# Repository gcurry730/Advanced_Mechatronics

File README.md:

# ME 433: Advanced Mechatronics

Gale Curry

3/31/16

This repository contains my code written for the course [ME 433](http://www.mccormick.northwestern.edu/mechanical/courses/descriptions/433-advanced-mechatronics.html) at Northwestern University. 
Most projects use the [PIC32MX250F128B](http://ww1.microchip.com/downloads/en/DeviceDoc/60001168H.pdf) microcontroller. 

### *HW 1*: **Breadboard Circuitry**
* Building a PIC32 circuit with voltage regulator + Hello World. 

### *HW 2 & 3*: **PCB Design**
* Design a PCB of the PIC32 circuit in EAGLE. 

### *HW 4*: **SPI & I2C Communication**
* Using SPI to communicate with a [MCP4902 DAC](http://www.microchip.com/wwwproducts/en/MCP4902). 
 
* Using I2C to communicate with a [MCP23008](http://www.microchip.com/wwwproducts/en/MCP23008) I/O pin expander.

### *HW 5*: **LCD**
* Writing Hello World to LCD. [128 x 128 pixel TFT LCD](http://www.gearbest.com/lcd-led-display-module/pp_219125.html)

### *HW 6*: **IMU**
* Read the [LSM6DS33](https://www.pololu.com/product/2736) IMU and write values to LCD. 

### *HW 7*: **USB**
* [MPLAB Harmony](http://www.microchip.com/mplab/mplab-harmony) project with USB; make the PIC32 enumerate as a mouse

### *HW 8*: **CDC**
* [MPLAB Harmony](http://www.microchip.com/mplab/mplab-harmony) CDC project; use PUTTY to send an int to the PIC32, and have it return the int

### *HW 9*: **Android Development**
* Write an Anrdoid App (Hello World). 

### *HW 10*: **3D Printing**
* Use CAD to make a wheel hub for your motor and o-ring. 3D print it.

### HW 11: **Laser Cutting**
* CAD a 3-sided box and laser cut it.

### *HW 12*: **Camera App**
* Write an Android app that uses the camera to identify the center of a brown line drawn on a green background.

### *HW 13*: **Android - CDC Communication**
* Write an Android app that communicates with a PIC32 CDC device.  

### *HW 14*: **Android - CDC Communication**  
* Write an Android app that mixes the camera and CDC apps together. 

### *HW 15*: **Motor Control** 
* Final line-following robot code. Final robot design.

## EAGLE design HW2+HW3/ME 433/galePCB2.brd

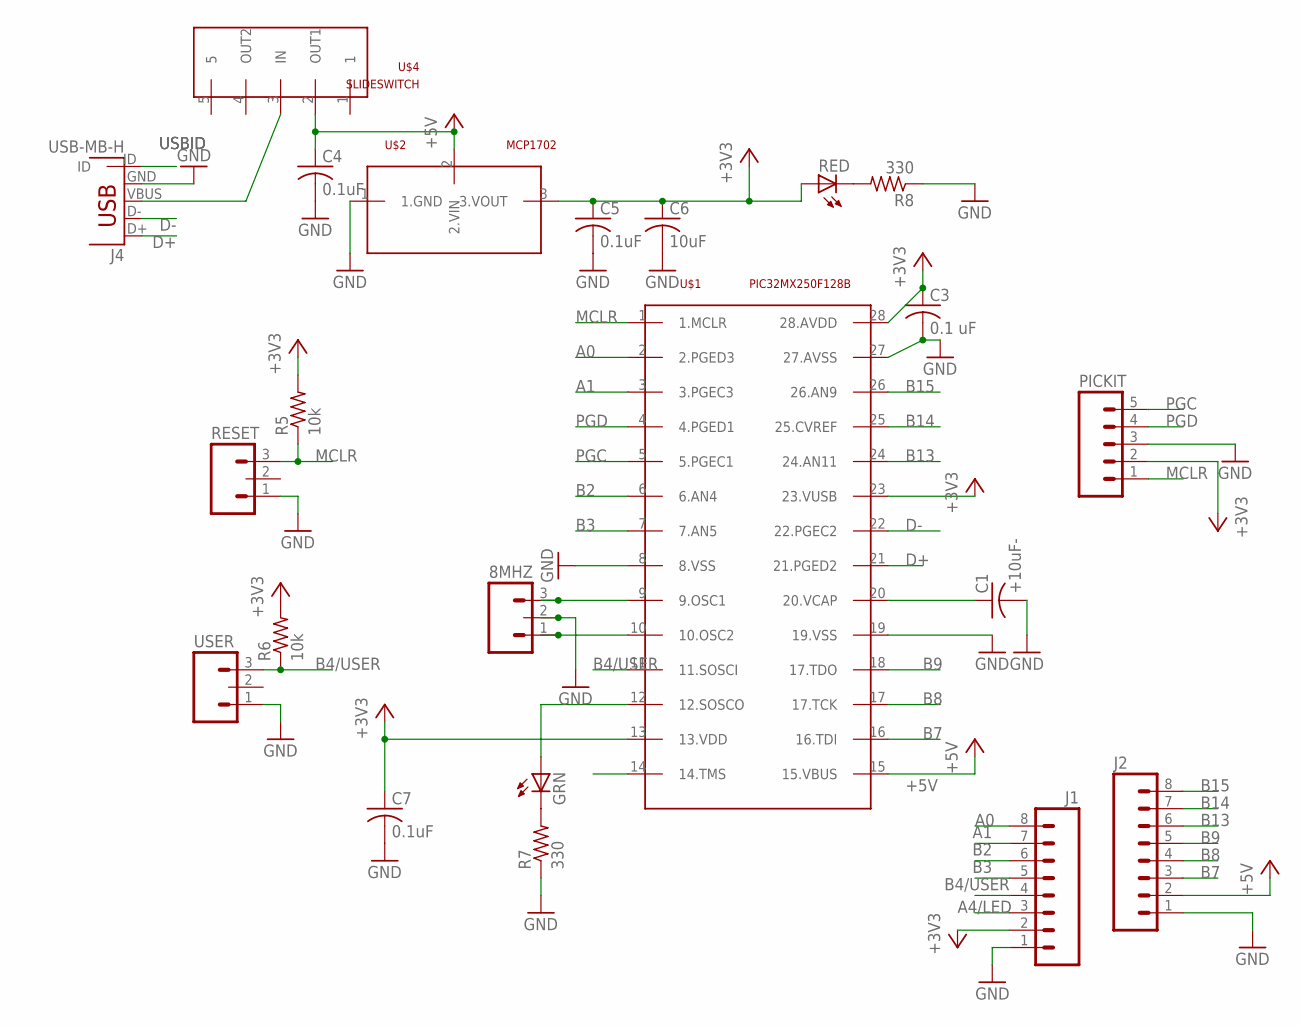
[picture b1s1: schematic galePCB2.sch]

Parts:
8MHZ: M03PTH; 1X03
C1: +10uF-; C025-024X044
C3: 0.1 uF; C025-024X044
C4, C5, C7: 0.1uF; C025-024X044
C6: 10uF; C025-024X044
GRN: LED3MM
J1, J2: M08; 1X08_ROUND
J4: USB-MB-H
PICKIT: M05PTH; 1X05
R5, R6: 10k; 0207/10
R7, R8: 330; 0207/10
RED: LED3MM
RESET: M03LOCK; 1X03_LOCK
U$1: PIC32MX250F128B; DIL28-3
U$2: MCP1702; TO92
U$4: SLIDESWITCH
USER: M03LOCK; 1X03_LOCK

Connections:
+3V3: C3.1, C5.1, C6.1, C7.1, J1.2, PICKIT.2, R5.2, R6.2, RED.A, U$1.13 (13.VDD), U$1.23 (23.VUSB), U$1.28 (28.AVDD), U$2.3 (3.VOUT)
+5V: C4.1, J2.2, U$1.15 (15.VBUS), U$2.2 (2.VIN), U$4.2 (OUT1)
A0: J1.8, U$1.2 (2.PGED3)
A1: J1.7, U$1.3 (3.PGEC3)
A4/LED: GRN.A, J1.3, U$1.12 (12.SOSCO)
B2: J1.6, U$1.6 (6.AN4)
B3: J1.5, U$1.7 (7.AN5)
B4/USER: J1.4, R6.1, U$1.11 (11.SOSCI), USER.3
B7: J2.3, U$1.16 (16.TDI)
B8: J2.4, U$1.17 (17.TCK)
B9: J2.5, U$1.18 (17.TDO)
B13: J2.6, U$1.24 (24.AN11)
B14: J2.7, U$1.25 (25.CVREF)
B15: J2.8, U$1.26 (26.AN9)
D+: J4.D+, U$1.21 (21.PGED2)
D-: J4.D-, U$1.22 (22.PGEC2)
GND: 8MHZ.2, C1.2, C3.2, C4.2, C5.2, C6.2, C7.2, J1.1, J2.1, J4.GND, PICKIT.3, R7.1, R8.1, RESET.1, U$1.8 (8.VSS), U$1.19 (19.VSS), U$1.27 (27.AVSS), U$2.1 (1.GND), USER.1
MCLR: PICKIT.1, R5.1, RESET.3, U$1.1 (1.MCLR)
unnamed: C1.1, U$1.20 (20.VCAP)
unnamed: 8MHZ.3, U$1.9 (9.OSC1)
unnamed: 8MHZ.1, U$1.10 (10.OSC2)
unnamed: R8.2, RED.K (C)
unnamed: GRN.K (C), R7.2
PGC: PICKIT.5, U$1.5 (5.PGEC1)
PGD: PICKIT.4, U$1.4 (4.PGED1)
USBID: J4.ID, U$1.14 (14.TMS)
VBUS: J4.VBUS, U$4.3 (IN)

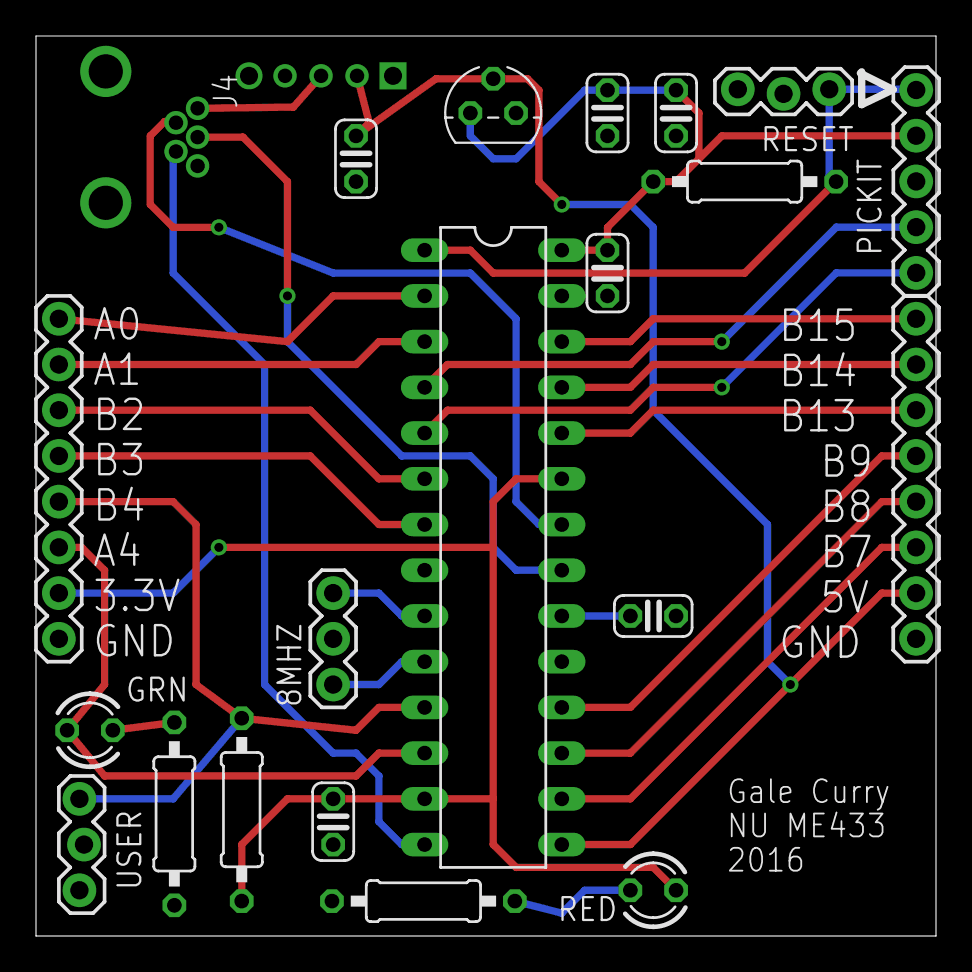
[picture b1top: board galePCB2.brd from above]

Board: 2 copper layers, 50.0 x 50.0 mm, 22 parts (1 on the bottom side), 27 nets.

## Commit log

2016-03-31 :circus_tent: Added .gitattributes & .gitignore files
2016-03-31 My first commit!
2016-03-31 Tester commit to see changes
2016-04-01 added scope pic for part 2
2016-04-01 Added scope photos as I added capacitors
    The first two each smoothed the oscillations more as I added them, the
    last one I added didn't make a noticeable difference
2016-04-04 Added picture of actual PIC32 circuit on breadboard
2016-04-04 Created a blank file for HW1 code
2016-04-04 added header files
2016-04-04 added values to #pragma values
2016-04-04 Made project file through MPLAB IDE
    Created a project in the IDE called HW1, made a main.c file and copied
    over my code that I was writing in the notepad
2016-04-05 complied code, first try
2016-04-05 Added circuit diagram
2016-04-06 added schematic in HW2 folder and updated HW1 code
2016-04-08 updated code
2016-04-08 Moved project into file, added completed library
2016-04-08 Added complete schematic
2016-04-14 Updated schematic % started making board layout
2016-04-14 Continued editing of board
    changed crystal oscillator to a M03, made all resistors smaller
2016-04-14 Finished Board positioning
    Flipped one of the M08 header pins around to align with given
    measurements, changed PICkit to a 5 pin header
2016-04-14 Board Fully connected
    May need to rotate switch, and need to write pin names on back of board
2016-04-14 making gerber files
2016-04-14 Ready to be checked before order
2016-04-18 Began HW4
    created I2C file with given code, started SPI file with functions that
    will be needed
2016-04-19 Moved files into MPLAB IDE and compiled
    finished functions for SPI communication
2016-04-20 Editing SPI still not working
2016-04-25 fixing SPI
2016-04-26 SPI working
2016-04-28 Making Sine and Triangle waves
    As seen in scope photo, the triangular wave is not going negative, the
    amplitude is also off. The sine wave has a discontinuity when the loop
    restarts.
2016-04-28 Fixed Sine wave, working on Triangle
    Sine wave now working, triangular wave is just a periodic spike
2016-05-05 Wrote I2C functions, re-checked PCB
2016-05-11 Finished Triangular wave
2016-05-12 Starting HW 5 w LCD
2016-05-13 Starting HW6 with IMU
    Also edited old hws
2016-05-17 Finished 3D printed wheels
2016-05-18 Hello World for Android completed
2016-05-19 Finished I2C
2016-05-20 Making Laser cut drawings
2016-05-23 Android app photo added
2016-05-23 Made first laser cuts + photo
2016-05-23 Changed SPI pins, LCD still not working
2016-05-24 Trying different pins for LCD with SPI again
2016-05-24 Started HW13
2016-05-27 Restarted LCD project from scratch
    Now able to talk to LCD!
2016-05-28 LCD printing text
2016-05-28 Removed old HW5 and started IMU functions
2016-05-28 Trying to get WHO_AM_I() to work
2016-05-31 Started HW 12
2016-06-01 Got camera app working with 4 lines
2016-06-01 HW12: have slider, not connected to threshold
2016-06-02 HW12 Completed
2016-06-02 WHO_AM_I function working
2016-06-02 printing IMU values to LCD
    getting weird values though
2016-06-03 HW8 finished
2016-06-04 AndroidCDC can connect to PIC
2016-06-05 Re-scaled IMU outputs
2016-06-05 Finished Laser cut bot (HW11)
2016-06-05 added dxf and CAD files to HW11
2016-06-05 added PWM to HW6
2016-06-05 Added photo to HW12
2016-06-06 Android receives msg from PIC
2016-06-06 HW13 completed
2016-06-07 HW14 working
2016-06-10 HW 15& 16
2016-09-24 img size test
2016-09-24 Resized images in readme
2016-09-24 resized images
2016-09-24 resize image
